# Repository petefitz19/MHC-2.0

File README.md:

# MHC-2.0
This repository contains the code for the second revision of the Midi Hand Controller Project

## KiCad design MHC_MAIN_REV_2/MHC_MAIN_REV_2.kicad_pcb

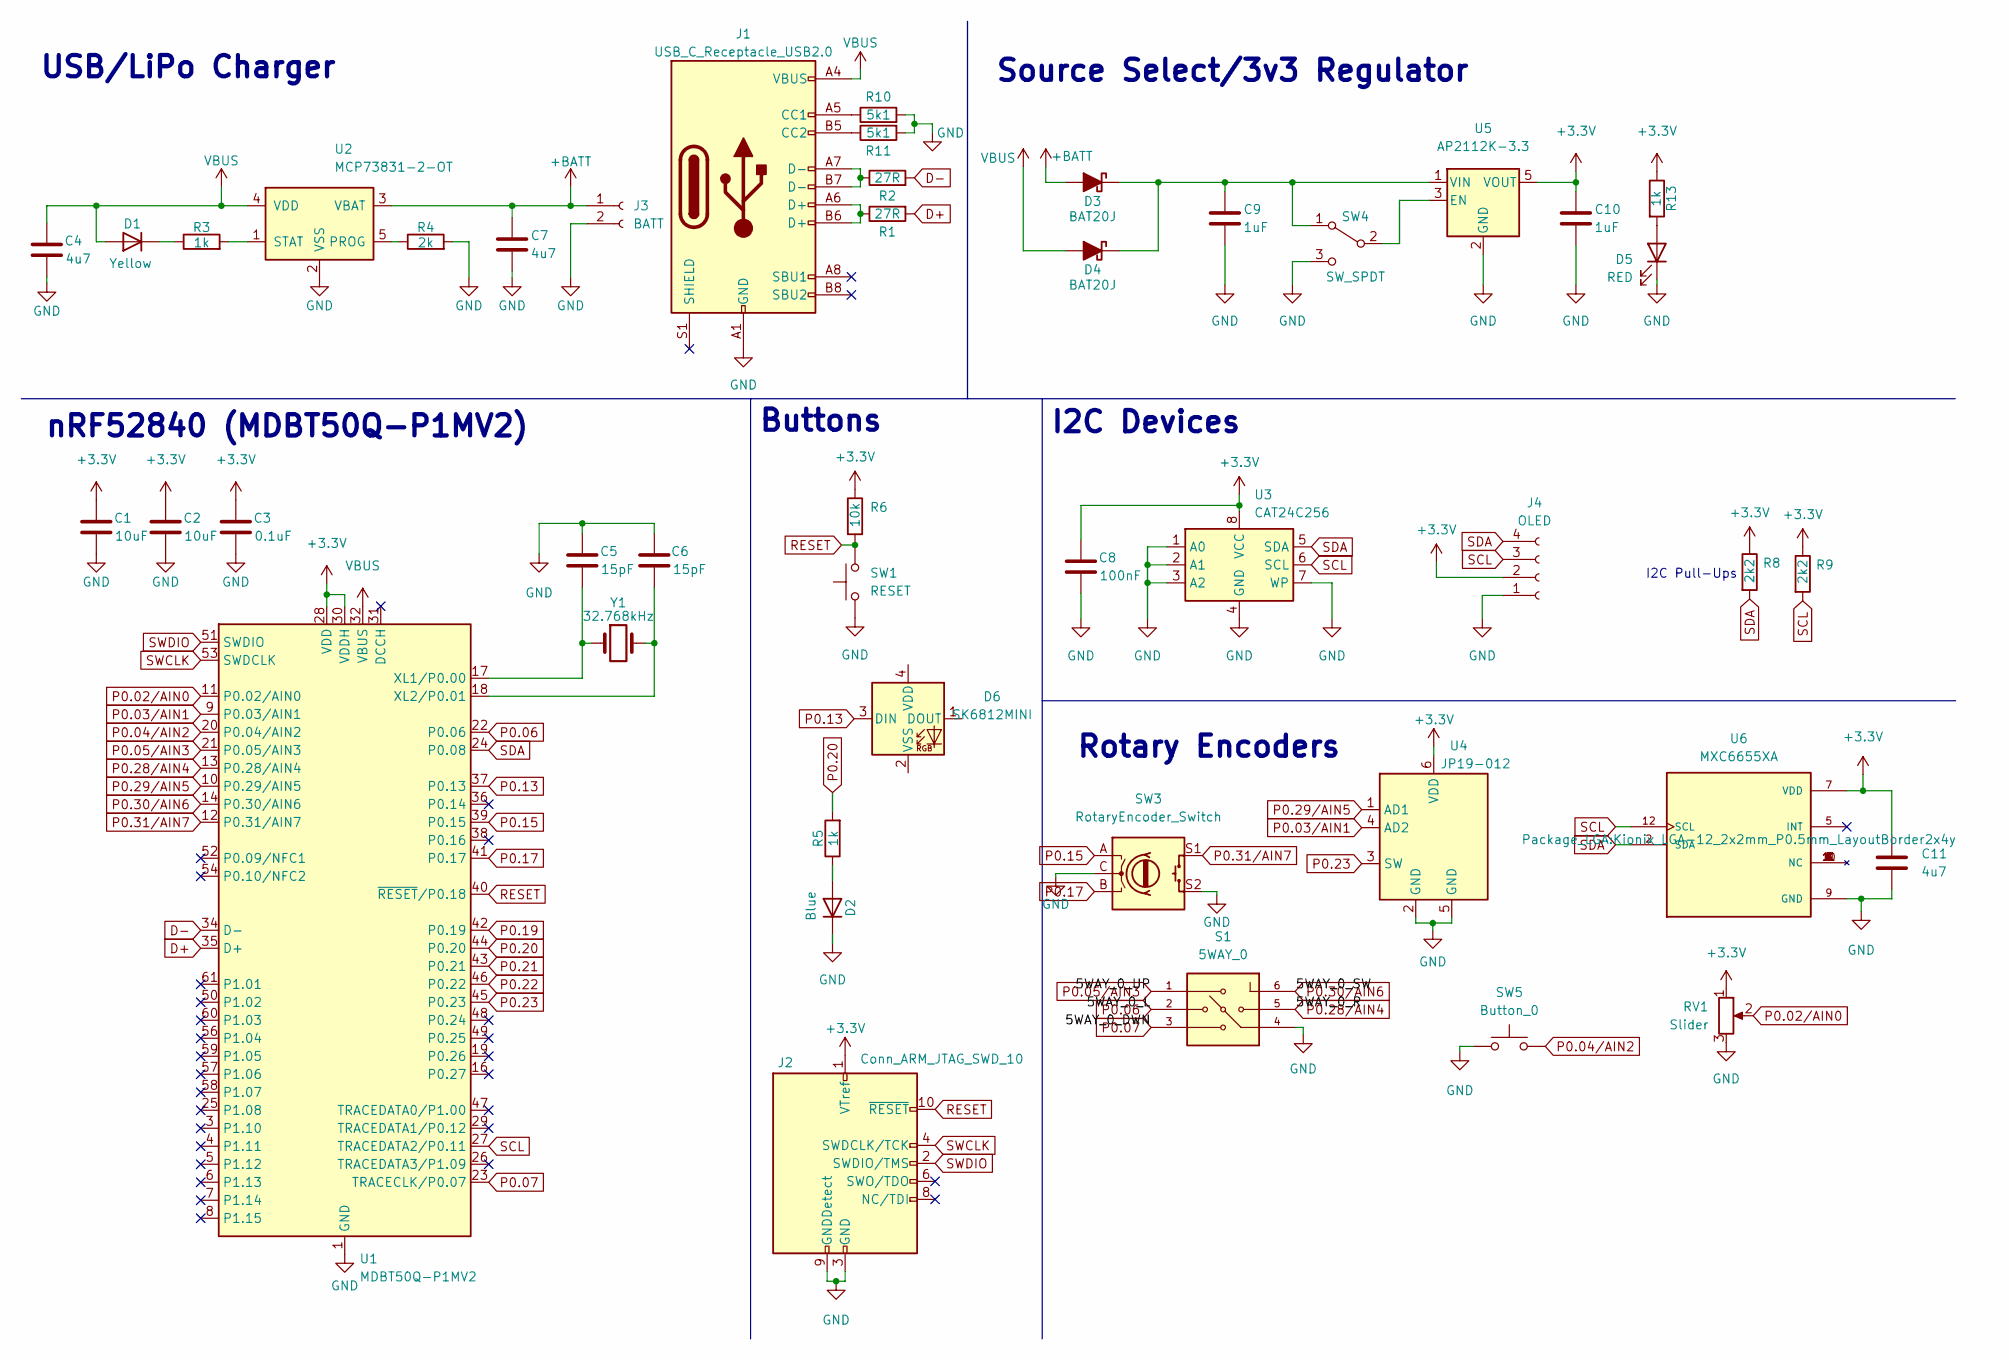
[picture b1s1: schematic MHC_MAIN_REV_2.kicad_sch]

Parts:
C1, C2: 10uF; C_0603_1608Metric; LCSC C1691
C3: 0.1uF; C_0603_1608Metric; LCSC C5128349
C4, C7: 4u7; C_0603_1608Metric; LCSC C907729
C5, C6: 15pF; C_0603_1608Metric; LCSC C107037
C8: 100nF; C_0402_1005Metric; LCSC C307331
C9, C10: 1uF; C_0603_1608Metric; LCSC C15849
C11: 4u7; C_0603_1608Metric; LCSC Part # C907729
D1: Yellow; LED_0603_1608Metric; LCSC C84264
D2: Blue; LED_0603_1608Metric; LCSC C72041
D3, D4: BAT20J; D_SOD-323; LCSC C155590
D5: RED; LED_0603_1608Metric
D6: SK6812MINI; LED_SK6812MINI_PLCC4_3.5x3.5mm_P1.75mm
J1: USB_C_Receptacle_USB2.0; USB_C_Receptacle_G-Switch_GT-USB-7010ASV
J2: Conn_ARM_JTAG_SWD_10; PinHeader_2x05_P1.27mm_Vertical
J3: BATT; JST_PH_S2B-PH-SM4-TB_1x02-1MP_P2.00mm_Horizontal
J4: OLED; PinHeader_1x04_P2.54mm_Vertical
R1, R2: 27R; R_0603_1608Metric
R3, R5, R13: 1k; R_0603_1608Metric; LCSC C21190
R4: 2k; R_0603_1608Metric; LCSC C22975
R6: 10k; R_0603_1608Metric; LCSC C25804
R8, R9: 2k2; R_0603_1608Metric; LCSC C2759747
R10, R11: 5k1; R_0603_1608Metric
RV1: Slider; Potentiometer_Bourns_PTA1543_Single_Slide
S1: 5WAY_0; SKQUCAA010
SW1: RESET; SW_Push_SPST_NO_Alps_SKRK
SW3: RotaryEncoder_Switch; RotaryEncoder_Alps_EC11E-Switch_Vertical_H20mm
SW4: SW_SPDT; PinHeader_1x03_P2.54mm_Vertical; LCSC C221841
SW5: Button_0; SW_Tactile_Straight_KSL0Axx1LFTR
U1: MDBT50Q-P1MV2; Raytac_MDBT50Q
U2: MCP73831-2-OT; SOT-23-5; LCSC C424093
U3: CAT24C256; SOIC-8_3.9x4.9mm_P1.27mm; LCSC C79987
U4: JP19-012
U5: AP2112K-3.3; SOT-23-5; LCSC C3021085
U6: MXC6655XA; Kionix_LGA-12_2x2mm_P0.5mm_LayoutBorder2x4y; LCSC C5189050
Y1: 32.768kHz; Crystal_SMD_3215-2Pin_3.2x1.5mm; LCSC C130253

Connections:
+3.3V: C1.1, C2.1, C3.1, C8.1, C10.1, C11.1, J2.1 (VTref), J4.2, R6.1, R8.1, R9.1, R13.1, RV1.1, U1.28 (VDD), U1.30 (VDDH), U3.8 (VCC), U4.6 (VDD), U5.5 (VOUT), U6.7 (VDD)
+BATT: C7.1, D3.2 (A), J3.1, U2.3 (VBAT)
D+: R1.2, U1.35 (D+)
D-: R2.2, U1.34 (D-)
GND: C1.2, C2.2, C3.2, C4.2, C5.1, C6.2, C7.2, C8.2, C9.2, C10.2, C11.2, D2.1 (K), D5.1 (K), J1.A1 (GND), J1.A12 (GND), J1.B1 (GND), J1.B12 (GND), J2.3 (GND), J2.5 (GND), J2.9 (GNDDetect), J3.2, J4.1, R4.2, R10.2, R11.2, RV1.3, S1.4, SW1.1, SW3.C, SW3.S2, SW4.3 (C), SW5.1, U1.1 (GND), U1.2 (GND), U1.15 (GND), U1.33 (GND), U1.55 (GND), U2.2 (VSS), U3.1 (A0), U3.2 (A1), U3.3 (A2), U3.4 (GND), U3.7 (WP), U4.2 (GND), U4.5 (GND), U5.2 (GND), U6.9 (GND)
unnamed: D1.1 (K), R3.1
unnamed: D2.2 (A), R5.1
unnamed: C9.1, D3.1 (K), D4.1 (K), SW4.1 (A), U5.1 (VIN)
unnamed: D5.2 (A), R13.2
unnamed: J1.A5 (CC1), R10.1
unnamed: J1.B5 (CC2), R11.1
unnamed: J1.A6 (D+), J1.B6 (D+), R1.1
unnamed: J1.A7 (D-), J1.B7 (D-), R2.1
unnamed: SW4.2 (B), U5.3 (EN)
unnamed: C5.2, U1.17 (XL1/P0.00), Y1.1
unnamed: C6.1, U1.18 (XL2/P0.01), Y1.2
unnamed: R4.1, U2.5 (PROG)
unnamed: R3.2, U2.1 (STAT)
P0.02/AIN0: RV1.2, U1.11 (P0.02/AIN0)
P0.03/AIN1: U1.9 (P0.03/AIN1), U4.4 (AD2)
P0.04/AIN2: SW5.2, U1.20 (P0.04/AIN2)
P0.05/AIN3: S1.1, U1.21 (P0.05/AIN3)
P0.06: S1.2, U1.22 (P0.06)
P0.07: S1.3, U1.23 (TRACECLK/P0.07)
P0.13: D6.3 (DIN), U1.37 (P0.13)
P0.15: SW3.A, U1.39 (P0.15)
P0.17: SW3.B, U1.41 (P0.17)
P0.19: U1.42 (P0.19)
P0.20: R5.2, U1.44 (P0.20)
P0.21: U1.43 (P0.21)
P0.22: U1.46 (P0.22)
P0.23: U1.45 (P0.23), U4.3 (SW)
P0.28/AIN4: S1.5, U1.13 (P0.28/AIN4)
P0.29/AIN5: U1.10 (P0.29/AIN5), U4.1 (AD1)
P0.30/AIN6: S1.6, U1.14 (P0.30/AIN6)
P0.31/AIN7: SW3.S1, U1.12 (P0.31/AIN7)
RESET: J2.10 (~RESET), R6.2, SW1.2, U1.40 (~RESET/P0.18)
SCL: J4.3, R9.2, U1.27 (TRACEDATA2/P0.11), U3.6 (SCL), U6.12 (SCL)
SDA: J4.4, R8.2, U1.24 (P0.08), U3.5 (SDA), U6.2 (SDA)
SWCLK: J2.4 (SWDCLK/TCK), U1.53 (SWDCLK)
SWDIO: J2.2 (SWDIO/TMS), U1.51 (SWDIO)
VBUS: C4.1, D1.2 (A), D4.2 (A), J1.A4 (VBUS), J1.A9 (VBUS), J1.B4 (VBUS), J1.B9 (VBUS), U1.32 (VBUS), U2.4 (VDD)

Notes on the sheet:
Source Select/3v3 Regulator
nRF52840 (MDBT50Q-P1MV2)
Rotary Encoders
USB/LiPo Charger
Buttons
I2C Pull-Ups
I2C Devices

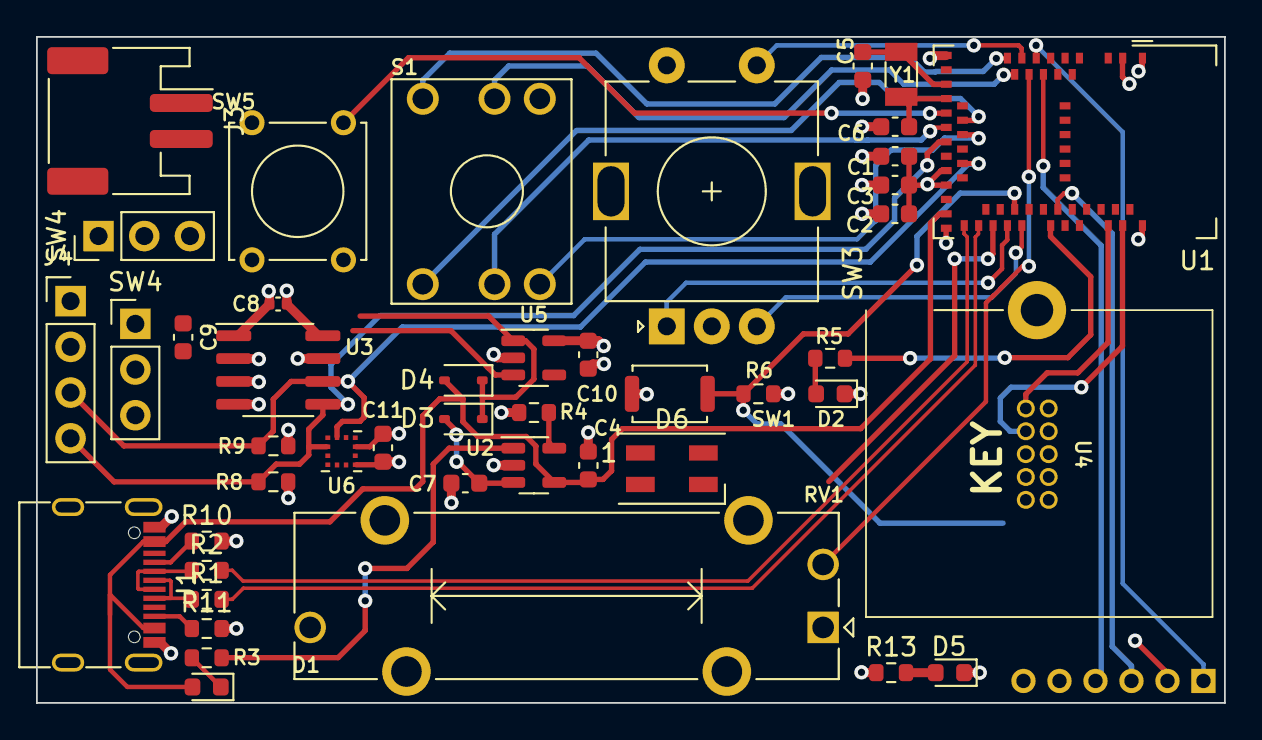
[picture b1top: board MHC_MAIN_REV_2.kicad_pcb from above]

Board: 4 copper layers, 66.0 x 37.0 mm, 46 parts (1 on the bottom side), 39 nets.

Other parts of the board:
SW4#2: SW_SPDT; PinHeader_1x03_P2.54mm_Vertical

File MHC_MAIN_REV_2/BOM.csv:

Comment,Designator,Footprint,LCSC,CoreStaff #,Digikey #
10uF,"C1,C2",Capacitor_SMD:C_0603_1608Metric,C1691,,
0.1uF,C3,Capacitor_SMD:C_0603_1608Metric,C5128349,,
4u7,"C4,C7,C11",Capacitor_SMD:C_0603_1608Metric, C907729,,
15pF,"C5,C6",Capacitor_SMD:C_0603_1608Metric,C107037,,
100nF,C8,Capacitor_SMD:C_0402_1005Metric,C307331,,
1uF,"C9,C10",Capacitor_SMD:C_0603_1608Metric,C15849,,
Yellow,D1,LED_SMD:LED_0603_1608Metric, C84264,,
BAT20J,"D2,D3",Diode_SMD:D_SOD-323,C155590,,
USB_B_Micro,J1,Connector_USB:USB_Micro-B_Molex_47346-0001, C132560,,
27R,"R1,R2",Resistor_SMD:R_0603_1608Metric,C25190,,
1k,R3,Resistor_SMD:R_0603_1608Metric,C21190,,
2k,R4,Resistor_SMD:R_0603_1608Metric,C22975,,
10k,"R5,R6",Resistor_SMD:R_0603_1608Metric,C25804,,
2k2,"R7,R8",Resistor_SMD:R_0603_1608Metric, C2759747,,
RESET,SW1,Button_Switch_SMD:SW_Push_SPST_NO_Alps_SKRK,,SKRKAEE020,
BOOT,SW2,Button_Switch_SMD:SW_Push_SPST_NO_Alps_SKRK,,SKRKAEE020,
SW_SPDT,SW4,Button_Switch_SMD:SW_SPDT_PCM12,C221841,,
MDBT50Q-P1MV2,U1,RF_Module:Raytac_MDBT50Q,,,3271-MDBT50Q-1MV2-ND
MCP73831-2-OT,U2,Package_TO_SOT_SMD:SOT-23-5,C424093,,
CAT24C256,U3,Package_SO:SOIC-8_3.9x4.9mm_P1.27mm,C79987,,
AP2112K-3.3,U5,Package_TO_SOT_SMD:SOT-23-5,C3021085,,
MXC6655XA,U6,Package_LGA:Kionix_LGA-12_2x2mm_P0.5mm_LayoutBorder2x4y,C5189050,,
32.768kHz,Y1,Crystal:Crystal_SMD_3215-2Pin_3.2x1.5mm,C130253,,

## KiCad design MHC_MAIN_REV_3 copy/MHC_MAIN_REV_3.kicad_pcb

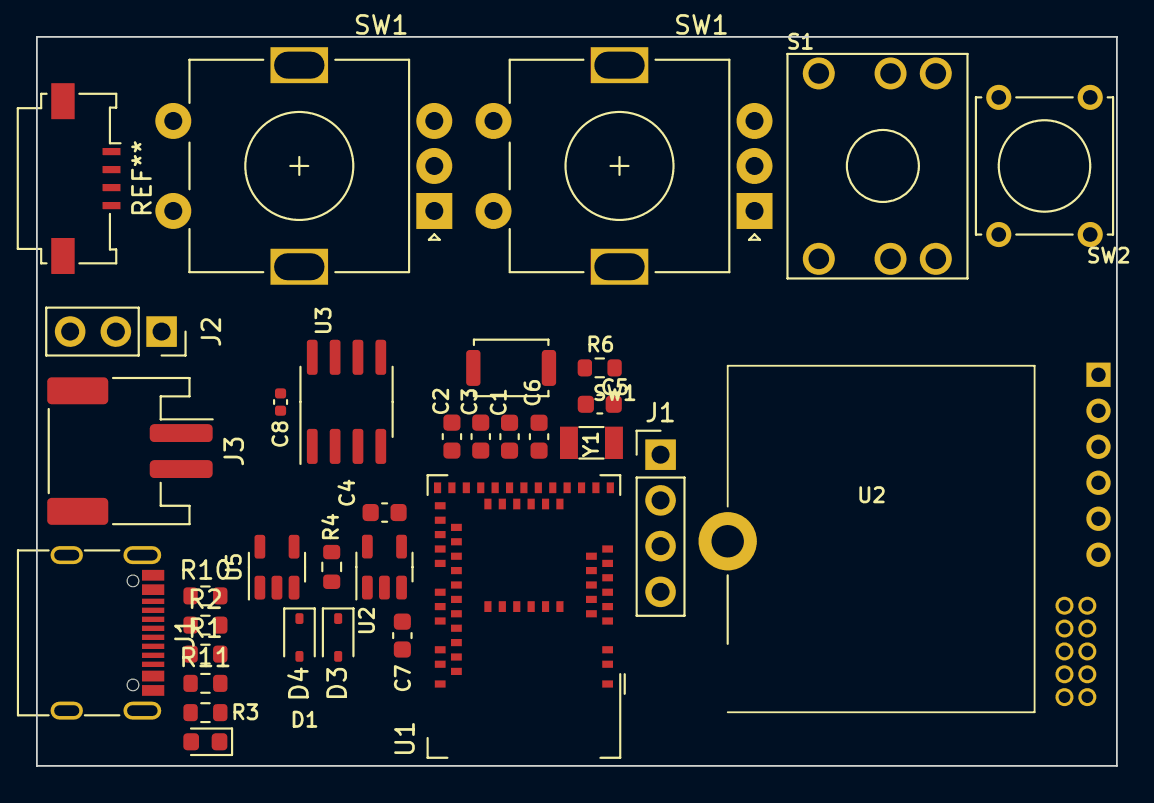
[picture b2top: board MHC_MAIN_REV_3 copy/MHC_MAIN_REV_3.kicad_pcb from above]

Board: 4 copper layers, 60.0 x 40.5 mm, 34 parts (1 on the bottom side), 17 nets, no tracks yet.

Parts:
C1, C2: 10uF; C_0603_1608Metric
C3: 0.1uF; C_0603_1608Metric
C4, C7: 4u7; C_0603_1608Metric
C5, C6: 15pF; C_0603_1608Metric
C8: 100nF; C_0402_1005Metric
D1: Yellow; LED_0603_1608Metric
D3, D4: BAT20J; D_SOD-323
J1: OLED; PinHeader_1x04_P2.54mm_Vertical
J1#2: USBC; USB_C_Receptacle_G-Switch_GT-USB-7010ASV
J2: LEDS; PinSocket_1x03_P2.54mm_Vertical
J2#2: Conn_ARM_JTAG_SWD_10; PinHeader_2x05_P1.27mm_Vertical
J3: BATT; JST_PH_S2B-PH-SM4-TB_1x02-1MP_P2.00mm_Horizontal
R1, R2: 27R; R_0603_1608Metric
R3: 1k; R_0603_1608Metric
R4: 2k; R_0603_1608Metric
R6: 10k; R_0603_1608Metric
R10, R11: 5k1; R_0603_1608Metric
S1: 5WAY_0; SKQUCAA010
SW1: RESET; SW_Push_SPST_NO_Alps_SKRK
SW1#2, SW1#3: RotaryEncoder_Switch; RotaryEncoder_Alps_EC11E-Switch_Vertical_H20mm
SW2: Button_0; SW_Tactile_Straight_KSL0Axx1LFTR
U1: MDBT50Q-P1MV2; Raytac_MDBT50Q
U2: MCP73831-2-OT; SOT-23-5
U2#2: JP19-012
U3: CAT24C256; SOIC-8_3.9x4.9mm_P1.27mm
U5: AP2112K-3.3; SOT-23-5
Y1: 32.768kHz; Crystal_SMD_3215-2Pin_3.2x1.5mm

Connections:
+3.3V: C1.1, C2.1, C3.1, C8.1, J1.2, J2#2.1 (VTref), R6.1, U1.28 (VDD), U1.30 (VDDH), U2#2.6 (VDD), U3.8 (VCC), U5.5 (VOUT)
GND: C1.2, C2.2, C3.2, C4.2, C5.1, C6.2, C7.2, C8.2, J1.1, J1#2.A1 (GND), J1#2.A12 (GND), J1#2.B1 (GND), J1#2.B12 (GND), J2#2.3 (GND), J2#2.5 (GND), J2#2.9 (GNDDetect), J3.2, R4.2, R10.2, R11.2, S1.4, SW1.1, SW1#3.C, SW1#3.S2, SW2.1, U1.1 (GND), U1.2 (GND), U1.15 (GND), U1.33 (GND), U1.55 (GND), U2.2 (VSS), U2#2.2 (GND), U2#2.5 (GND), U3.1 (A0), U3.2 (A1), U3.3 (A2), U3.4 (GND), U3.7 (WP), U5.2 (GND)
unnamed: D1.1 (K), R3.1
P0.03/AIN1: U1.9 (P0.03/AIN1), U2#2.4 (AD2)
P0.04/AIN2: SW2.2, U1.20 (P0.04/AIN2)
P0.05/AIN3: S1.1, U1.21 (P0.05/AIN3)
P0.06: S1.2, U1.22 (P0.06)
P0.07: S1.3, U1.23 (TRACECLK/P0.07)
P0.15: SW1#3.A, U1.39 (P0.15)
P0.17: SW1#3.B, U1.41 (P0.17)
P0.23: U1.45 (P0.23), U2#2.3 (SW)
P0.28/AIN4: S1.5, U1.13 (P0.28/AIN4)
P0.29/AIN5: U1.10 (P0.29/AIN5), U2#2.1 (AD1)
P0.30/AIN6: S1.6, U1.14 (P0.30/AIN6)
P0.31/AIN7: SW1#3.S1, U1.12 (P0.31/AIN7)
SCL: J1.3, U1.27 (TRACEDATA2/P0.11), U3.6 (SCL)
SDA: J1.4, U1.24 (P0.08), U3.5 (SDA)

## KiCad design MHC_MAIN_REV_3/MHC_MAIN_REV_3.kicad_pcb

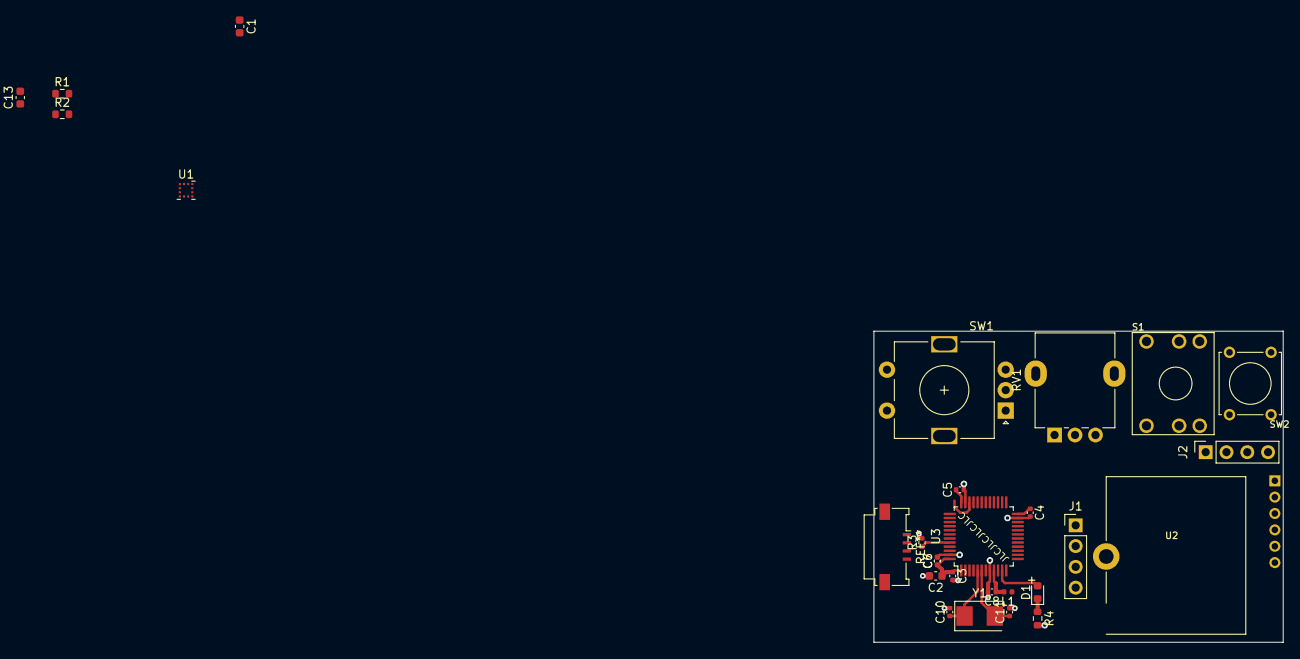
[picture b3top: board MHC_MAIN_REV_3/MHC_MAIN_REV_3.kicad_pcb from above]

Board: 4 copper layers, 50.0 x 38.0 mm, 27 parts (0 on the bottom side), 11 nets.

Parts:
C1: 0.1uF; C_0603_1608Metric
C2, C13: 4u7; C_0603_1608Metric
C3, C4, C5, C6, C8: 100n; C_0402_1005Metric
C7: 1u; C_0402_1005Metric
C10, C11: 30p; C_0402_1005Metric
D1: BLUE; LED_0603_1608Metric
J1: OLED; PinHeader_1x04_P2.54mm_Vertical
J2: JLINK; PinSocket_1x04_P2.54mm_Vertical
L1: 27n; L_0402_1005Metric
R1, R2: 2k2; R_0603_1608Metric
R3: 10k; R_0402_1005Metric
R4: 1k5; R_0603_1608Metric
RV1: Slider; Potentiometer_Alpha_RD901F-40-00D_Single_Vertical
S1: 5WAY_0; SKQUCAA010
SW1: RotaryEncoder_Switch; RotaryEncoder_Alps_EC11E-Switch_Vertical_H20mm
SW2: Button_0; SW_Tactile_Straight_KSL0Axx1LFTR
U1: MXC6655XA; Kionix_LGA-12_2x2mm_P0.5mm_LayoutBorder2x4y
U2: JP19-012
U3: STM32F103C8T6; LQFP-48_7x7mm_P0.5mm
Y1: 8MHz; Crystal_SMD_5032-2Pin_5.0x3.2mm

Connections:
+3.3V: C2.1, C3.1, C4.1, C5.1, C6.1, C13.1, J1.2, L1.1, R1.1, R2.1, RV1.1, U1.7 (VDD), U2.6 (VDD), U3.1 (VBAT), U3.24 (VDD), U3.36 (VDD), U3.48 (VDD)
+3.3VA: C7.1, C8.1, L1.2, U3.9 (VDDA)
/BOOT0: R3.1, U3.44 (BOOT0)
/HSE_IN: C11.1, U3.6 (PD1), Y1.2
/HSE_OUT: C10.1, U3.5 (PD0), Y1.1
/LED_STAT: D1.2 (A), U3.34 (PA13)
/VCC: C1.1, J2.1
GND: C1.2, C2.2, C3.2, C4.2, C5.2, C6.2, C7.2, C8.2, C10.2, C11.2, C13.2, J1.1, J2.4, R3.2, R4.2, RV1.3, S1.4, SW1.C, SW1.S2, SW2.1, U1.9 (GND), U2.2 (GND), U2.5 (GND), U3.8 (VSSA), U3.23 (VSS), U3.35 (VSS), U3.47 (VSS)
unnamed: D1.1 (K), R4.1
SCL: J1.3, R2.2, U1.12 (SCL)
SDA: J1.4, R1.2, U1.2 (SDA)

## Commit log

2022-12-08 Initial Commit (Blank STM32CubeIDE C++ project)
2022-12-08 Added in Configured IOC and steps to reproduce in IOC_Setup.txt
2022-12-08 Renamed main.c to main.cpp and confirmed USART is working
2022-12-10 Added in Potentiometer functionality
2022-12-10 Added in RotaryEncoder functionality
2023-01-07 Got MIDI working, Switched I2C to I2C2
2023-01-10 Changed HSE to 16 MHz. Currently running MIDI sample on new board
2023-05-28 Adding files for MHC_REV_2
2023-06-19 Added Baseline Arduino code
2023-09-07 Added MHC_Programmer_App
2023-11-07 Fixed several bugs after initial test run
2023-11-19 Add temporary fix for logic being the opposite for binary midi components
2024-01-21 Updating git repo for Arduino code
2024-01-22 Updating MHC files
2024-03-06 Joystick and Slider improvements. Pitch bend support
2024-03-11 Added pitch bend option
2024-03-14 Added executables for app
